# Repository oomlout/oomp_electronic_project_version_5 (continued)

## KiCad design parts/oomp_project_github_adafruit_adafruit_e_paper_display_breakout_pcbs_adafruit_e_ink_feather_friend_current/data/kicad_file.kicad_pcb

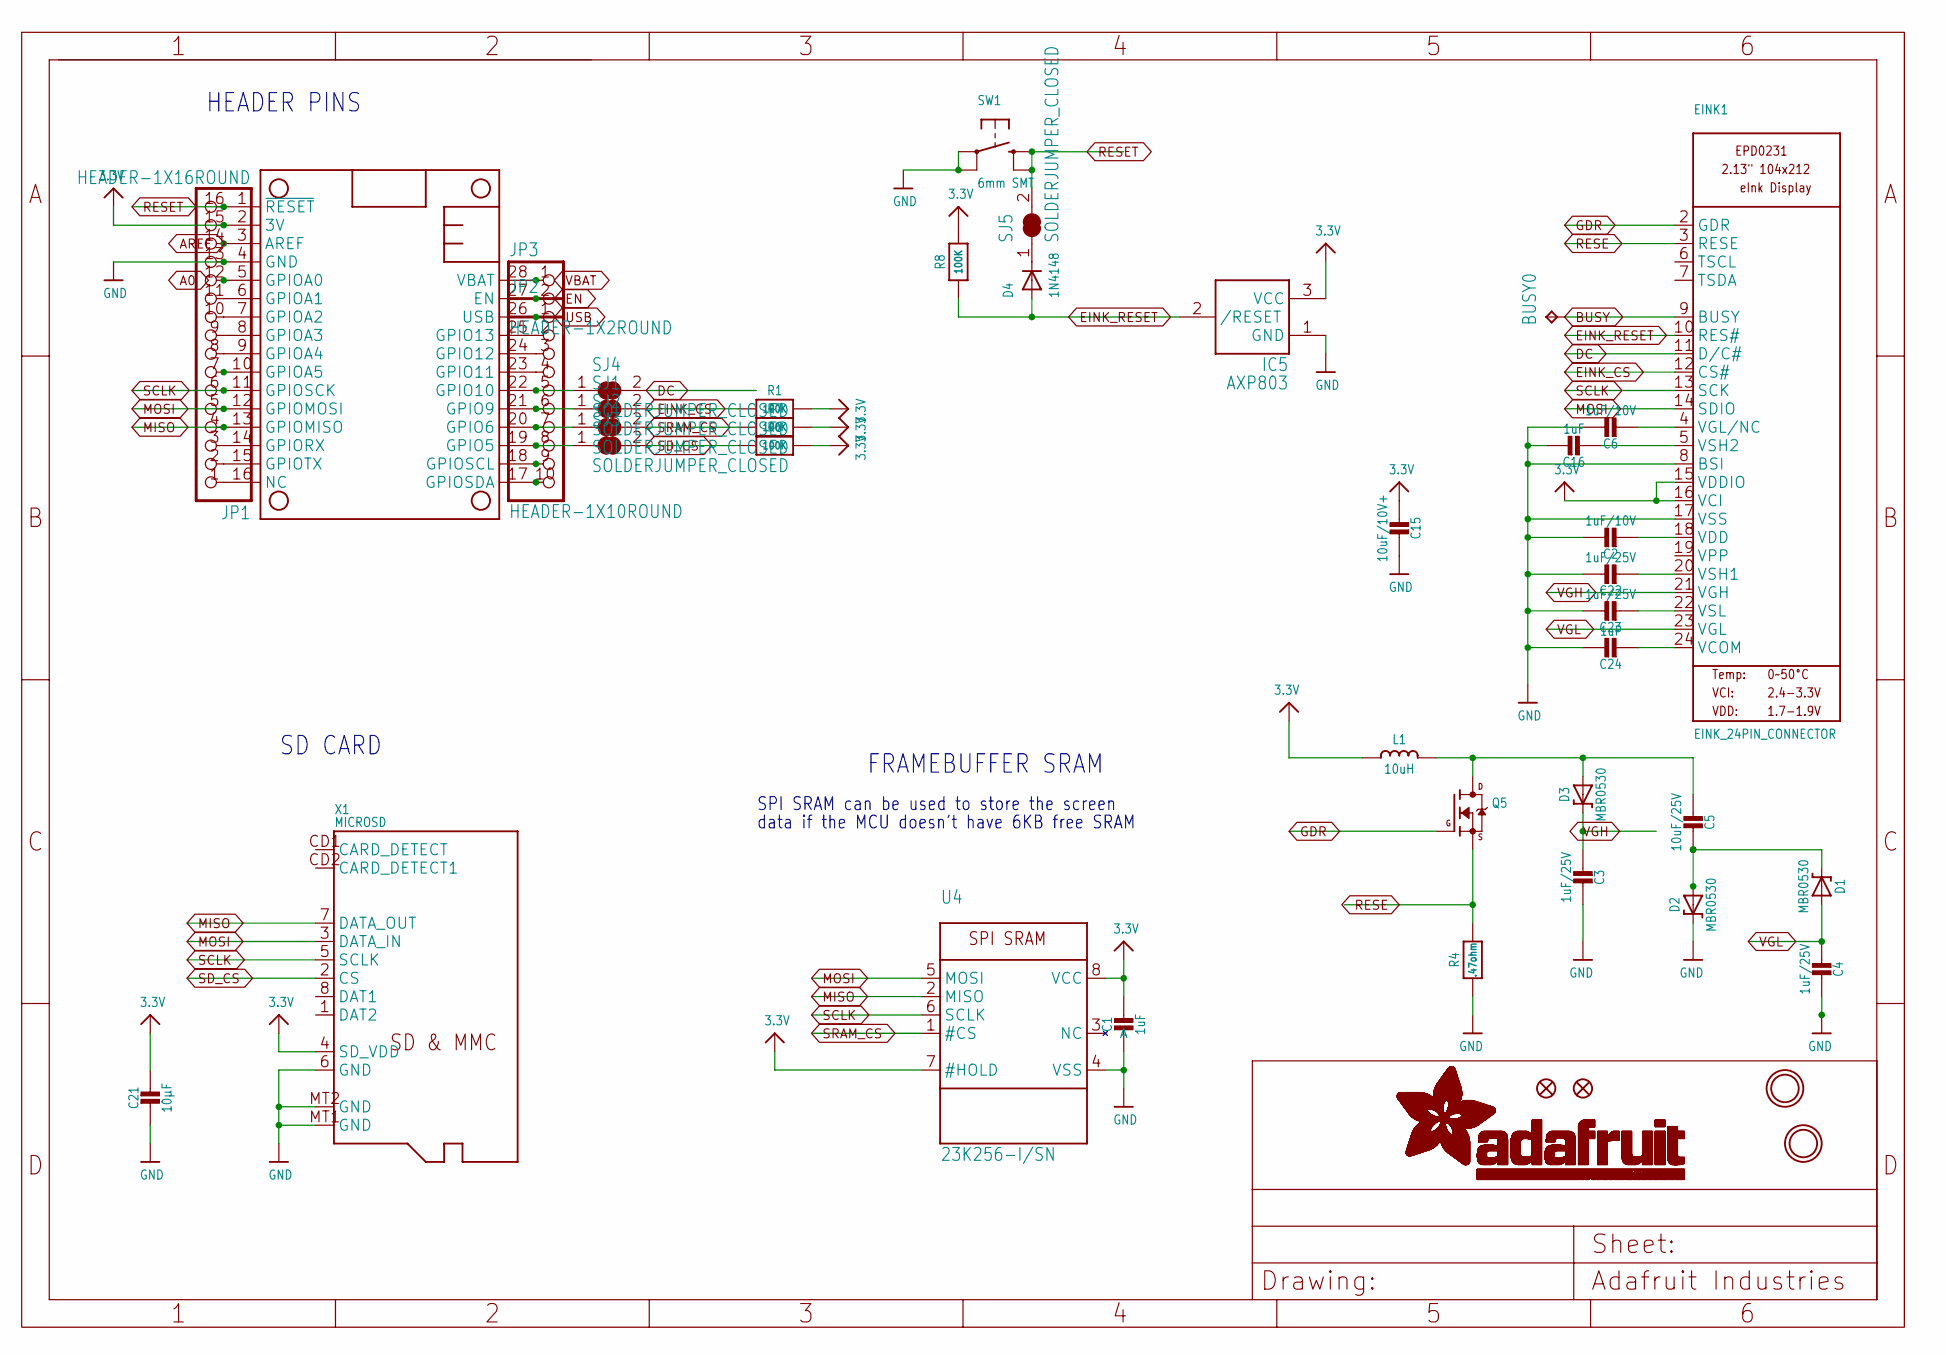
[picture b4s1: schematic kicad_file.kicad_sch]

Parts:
BUSY0: TPTP15SQ; TP15SQ
C1: 1uF; 0805_10MGAP
C2, C6: 1uF/10V; 0805-NO
C3, C4, C22, C23: 1uF/25V; 0805-NO
C5: 10uF/25V; 0805-NO
C15: 10uF/10V+; 0805-NO
C16, C24: 1uF; 0805-NO
C21: 10µF; 0805-NO
D1, D2, D3: MBR0530; SOD-123
D4: 1N4148; SOD-323F
EINK1: EINK_24PIN_CONNECTOR; EINK_24PIN
FID1, FID3: FIDUCIAL_1MM
IC5: AXP803; SOT23
JP1: HEADER-1X16ROUND; 1X16_ROUND
JP2: HEADER-1X10ROUND; 1X10_ROUND
JP3: HEADER-1X2ROUND; 1X02_ROUND
L1: 10uH; INDUCTOR_4X4MM_NR401
MS1: FEATHERWING_NOHOLES
Q5: IRLML0100; SOT23-3
R1, R6, R7, R8: 100K; 0603-NO
R4: .47ohm; 0805_10MGAP
SJ1, SJ2, SJ3, SJ4, SJ5: SOLDERJUMPER_CLOSED; SOLDERJUMPER_CLOSEDWIRE
SW1: 6mm SMT; BTN_KMR2_4.6X2.8
U4: 23K256-I/SN; SOIC8_150MIL
U$3, U$4: MOUNTINGHOLE2.5; MOUNTINGHOLE_2.5_PLATED
X1: MICROSD

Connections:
3.3V: C1.1, C15.2, C21.1, EINK1.15 (VDDIO), EINK1.16 (VCI), IC5.3 (VCC), JP1.15, L1.P$2 (2), MS1.2 (3V), R1.2, R6.2, R7.2, R8.2, U4.7 (#HOLD), U4.8 (VCC), X1.4 (SD_VDD)
A0: JP1.12, MS1.5 (GPIOA0)
AREF: JP1.14, MS1.3 (AREF)
BUSY: BUSY0.TP, EINK1.9 (BUSY)
DC: EINK1.11 (D/C#), SJ4.2
EINK_CS: EINK1.12 (CS#), R1.1, SJ1.2
EINK_RESET: D4.A, EINK1.10 (RES#), IC5.2 (/RESET), R8.1
EN: JP3.2, MS1.27 (EN)
GDR: EINK1.2 (GDR), Q5.1 (G)
GND: C1.2, C2.1, C3.2, C4.2, C6.1, C15.1, C16.1, C21.2, C22.1, C23.1, C24.1, D2.C, EINK1.8 (BSI), EINK1.17 (VSS), IC5.1 (GND), JP1.13, MS1.4 (GND), R4.2, SW1.A, SW1.A' (P1), U4.4 (VSS), X1.6 (GND), X1.MT1 (GND), X1.MT2 (GND)
H: JP2.8, MS1.19 (GPIO5), SJ3.1
I: JP2.7, MS1.20 (GPIO6), SJ2.1
J: JP2.6, MS1.21 (GPIO9), SJ1.1
K: JP2.5, MS1.22 (GPIO10), SJ4.1
MISO: JP1.4, MS1.13 (GPIOMISO), U4.2 (MISO), X1.7 (DATA_OUT)
MOSI: EINK1.14 (SDIO), JP1.5, MS1.12 (GPIOMOSI), U4.5 (MOSI), X1.3 (DATA_IN)
unnamed: JP1.7, MS1.10 (GPIOA5)
unnamed: C5.2, D1.C, D2.A
unnamed: C5.1, D3.A, L1.P$1 (1), Q5.3 (D)
unnamed: C16.2, EINK1.5 (VSH2)
unnamed: C2.2, EINK1.18 (VDD)
unnamed: C22.2, EINK1.20 (VSH1)
unnamed: D4.C, SJ5.1
unnamed: JP1.11, MS1.6 (GPIOA1)
unnamed: C6.2, EINK1.4 (VGL/NC)
unnamed: JP1.10, MS1.7 (GPIOA2)
unnamed: JP1.9, MS1.8 (GPIOA3)
unnamed: JP1.8, MS1.9 (GPIOA4)
unnamed: JP1.3, MS1.14 (GPIORX)
unnamed: JP1.2, MS1.15 (GPIOTX)
unnamed: JP1.1, MS1.16 (NC)
unnamed: JP2.10, MS1.17 (GPIOSDA)
unnamed: JP2.9, MS1.18 (GPIOSCL)
unnamed: JP2.4, MS1.23 (GPIO11)
unnamed: JP2.3, MS1.24 (GPIO12)
unnamed: JP2.2, MS1.25 (GPIO13)
unnamed: C23.2, EINK1.22 (VSL)
unnamed: C24.2, EINK1.24 (VCOM)
RESE: EINK1.3 (RESE), Q5.2 (S), R4.1
RESET: JP1.16, MS1.1 (~RESET), SJ5.2, SW1.B (S), SW1.B' (S1)
SCLK: EINK1.13 (SCK), JP1.6, MS1.11 (GPIOSCK), U4.6 (SCLK), X1.5 (SCLK)
SD_CS: R6.1, SJ3.2, X1.2 (CS)
SRAM_CS: R7.1, SJ2.2, U4.1 (#CS)
USB: JP2.1, MS1.26 (USB)
VBAT: JP3.1, MS1.28 (VBAT)
VGH: C3.1, D3.C, EINK1.21 (VGH)
VGL: C4.1, D1.A, EINK1.23 (VGL)

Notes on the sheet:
FRAMEBUFFER SRAM
SPI SRAM can be used to store the screen
data if the MCU doesn't have 6KB free SRAM
HEADER PINS
SD CARD

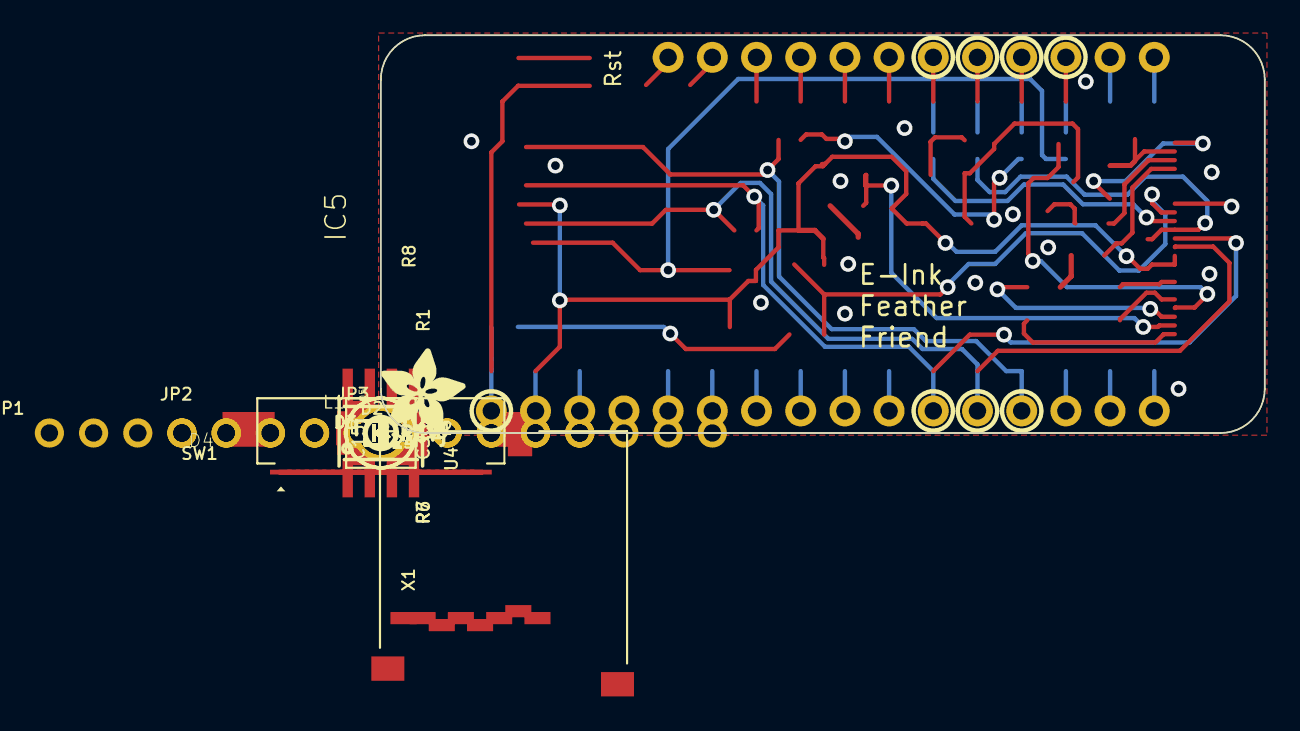
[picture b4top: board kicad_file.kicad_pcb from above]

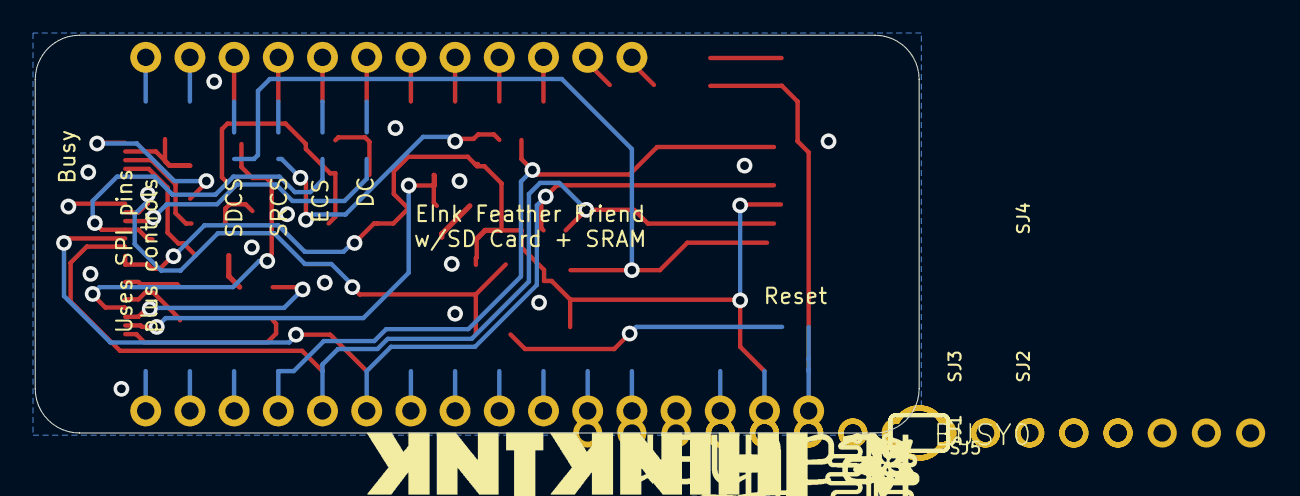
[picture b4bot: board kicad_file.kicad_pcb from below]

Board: 2 copper layers, 50.8 x 22.9 mm, 47 parts (9 on the bottom side), 47 nets.

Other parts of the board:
U$5: THINKINK_1.25IN
U$6: FEATHERLOGO_MED
U$8: ADAFRUIT_5MM
U$9: PCBFEAT-REV-040
U$17: ADAFRUIT_3.5MM

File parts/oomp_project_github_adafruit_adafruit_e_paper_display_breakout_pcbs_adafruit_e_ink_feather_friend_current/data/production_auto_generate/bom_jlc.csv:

Comment,Designator,Footprint,LCSC Part #
,JP3,Adafruit eInk Feather Friend-import-fps:1X02_ROUND,C492401
,JP2,Adafruit eInk Feather Friend-import-fps:1X10_ROUND,C57369
,JP1,Adafruit eInk Feather Friend-import-fps:1X16_ROUND,C7501270
,U$17,Adafruit eInk Feather Friend-import-fps:ADAFRUIT_3.5MM,
,U$8,Adafruit eInk Feather Friend-import-fps:ADAFRUIT_5MM,
,U$6,Adafruit eInk Feather Friend-import-fps:FEATHERLOGO_MED,
,U$9,Adafruit eInk Feather Friend-import-fps:PCBFEAT-REV-040,
,U$5,Adafruit eInk Feather Friend-import-fps:THINKINK_1.25IN,
.47ohm,R4,Adafruit eInk Feather Friend-import-fps:0805_10MGAP,
100K,"R1,R6,R7,R8",Adafruit eInk Feather Friend-import-fps:0603-NO,C25803
10uF/10V+,C15,Adafruit eInk Feather Friend-import-fps:0805-NO,
10uF/25V,C5,Adafruit eInk Feather Friend-import-fps:0805-NO,
10uH,L1,Adafruit eInk Feather Friend-import-fps:INDUCTOR_4X4MM_NR401,
10µF,C21,Adafruit eInk Feather Friend-import-fps:0805-NO,
1N4148,D4,Adafruit eInk Feather Friend-import-fps:SOD-323F,
1uF,"C16,C24",Adafruit eInk Feather Friend-import-fps:0805-NO,
1uF,C1,Adafruit eInk Feather Friend-import-fps:0805_10MGAP,
1uF/10V,"C2,C6",Adafruit eInk Feather Friend-import-fps:0805-NO,
1uF/25V,"C3,C4,C22,C23",Adafruit eInk Feather Friend-import-fps:0805-NO,
23K256-I/SN,U4,Adafruit eInk Feather Friend-import-fps:SOIC8_150MIL,
6mm SMT,SW1,Adafruit eInk Feather Friend-import-fps:BTN_KMR2_4.6X2.8,
AXP803,IC5,Adafruit eInk Feather Friend-import-fps:SOT23,
EINK_24PIN_CONNECTOR,EINK1,Adafruit eInk Feather Friend-import-fps:EINK_24PIN,
FEATHERWING_NOHOLES,MS1,Adafruit eInk Feather Friend-import-fps:FEATHERWING_NOHOLES,
IRLML0100,Q5,Adafruit eInk Feather Friend-import-fps:SOT23-3,
MBR0530,"D1,D2,D3",Adafruit eInk Feather Friend-import-fps:SOD-123,
MICROSD,X1,Adafruit eInk Feather Friend-import-fps:MICROSD,
TPTP15SQ,BUSY0,Adafruit eInk Feather Friend-import-fps:TP15SQ,

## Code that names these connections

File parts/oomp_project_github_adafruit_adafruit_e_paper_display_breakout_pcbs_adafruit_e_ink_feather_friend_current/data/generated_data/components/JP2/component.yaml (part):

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      connected_to:
      - reference: MS1
        pin_number: '25'
        pin_name: GPIO13
    - number: '3'
      name: '3'
      electrical_type: passive
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      connected_to:
      - reference: MS1
        pin_number: '24'
        pin_name: GPIO12
    - number: '4'
      name: '4'
      electrical_type: passive
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      connected_to:
      - reference: MS1
        pin_number: '23'
        pin_name: GPIO11
    - number: '5'
      name: '5'
      electrical_type: passive
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      connected_to:
      - reference: MS1
        pin_number: '22'
        pin_name: GPIO10
      - reference: SJ4
        pin_number: '1'
        pin_name: '1'
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      connected_to:
      - reference: MS1
        pin_number: '21'
        pin_name: GPIO9
      - reference: SJ1
        pin_number: '1'
        pin_name: '1'
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      connected_to:
      - reference: MS1
        pin_number: '20'
        pin_name: GPIO6
      - reference: SJ2
        pin_number: '1'
        pin_name: '1'
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      connected_to:
      - reference: MS1
        pin_number: '19'
        pin_name: GPIO5
      - reference: SJ3
        pin_number: '1'
        pin_name: '1'
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    pin_name: GPIOSCL
  - reference: MS1
    pin_number: '19'
    pin_name: GPIO5
  - reference: MS1
    pin_number: '20'
    pin_name: GPIO6
  - reference: MS1
    pin_number: '21'
    pin_name: GPIO9
  - reference: MS1
    pin_number: '22'
    pin_name: GPIO10
  - reference: MS1
    pin_number: '23'
    pin_name: GPIO11
  - reference: MS1
    pin_number: '24'
    pin_name: GPIO12
  - reference: MS1
    pin_number: '25'
    pin_name: GPIO13
  - reference: MS1
    pin_number: '26'
    pin_name: USB
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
